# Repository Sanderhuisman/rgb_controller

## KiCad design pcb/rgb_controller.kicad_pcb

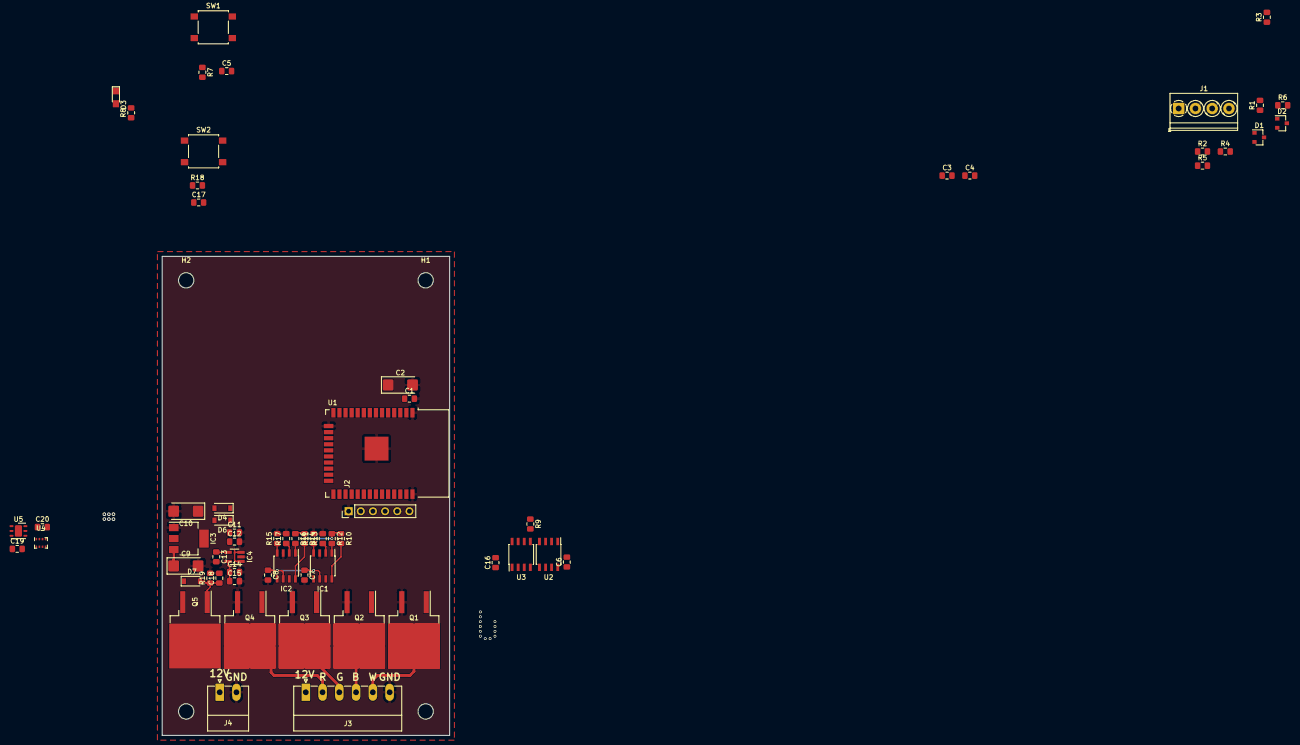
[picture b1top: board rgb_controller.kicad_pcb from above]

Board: 2 copper layers, 60.0 x 100.0 mm, 69 parts (0 on the bottom side), 40 nets.

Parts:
C1, C3, C4, C5, C6, C12, C15, C16, C17, C19, C20: 100nF; C_0805_2012Metric_Pad1.15x1.40mm_HandSolder
C2, C9, C10: 10uF; CP_EIA-6032-28_Kemet-C_Pad2.25x2.35mm_HandSolder
C7, C8: 1uF X7R; C_0805_2012Metric_Pad1.15x1.40mm_HandSolder
C11, C14: 1uF X5R; C_0805_2012Metric_Pad1.15x1.40mm_HandSolder
C13: 10nF X7R; C_0805_2012Metric_Pad1.15x1.40mm_HandSolder
C18: 15nF; C_0805_2012Metric_Pad1.15x1.40mm_HandSolder
D1, D2: BAT54S; SOT-23
D3: RED; LED_0805_HandSoldering
D4, D6: MBR0520; D_SOD-123
D7: MMSZ5240BT1G; D_SOD-123
H1, H2, H3, H4: MountingHole; MountingHole_3.2mm_M3
IC1, IC2: PM8834; SOIC-8_3.9x4.9mm_Pitch1.27mm
IC3: LD1117S50TR_SOT223; SOT-223-3_TabPin2
IC4: LD3985M33R_SOT23; SOT-23-5_HandSoldering
J1: Screw_Terminal_01x04; TerminalBlock_Phoenix_PT-1,5-4-3.5-H_1x04_P3.50mm_Horizontal
J2: COM; Pin_Header_Straight_1x06_Pitch2.54mm
J3: Screw_Terminal_01x06; PhoenixContact_MC-G_06x3.50mm_Angled
J4: Screw_Terminal_01x02; PhoenixContact_MC-G_02x3.50mm_Angled
Q1, Q2, Q3, Q4: IRF3205SPBF; TO-263-2
Q5: IRF9540N; TO-263-2
R1, R4: 10R; R_0805_2012Metric_Pad1.15x1.40mm_HandSolder
R2, R5, R8: 1K; R_0805_2012Metric_Pad1.15x1.40mm_HandSolder
R3, R6, R7, R9, R10, R11, R12, R13, R14, R15, R16, R17, R18, R19: 10K; R_0805_2012Metric_Pad1.15x1.40mm_HandSolder
SW1, SW2: SW_Push; SW_SPST_B3S-1000
U1: ESP32-WROOM-32D; ESP32-WROOM-32
U2: LM75B; SOIC-8_3.9x4.9mm_P1.27mm
U3: TSL2550D; SOIC-8_3.9x4.9mm_Pitch1.27mm
U4: BMP280; Bosch_LGA-8_2x2.5mm_P0.65mm_ClockwisePinNumbering
U5: Si7021-A20; DFN-6-1EP_3x3mm_P1mm_EP1.5x2.4mm

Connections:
+3V3: C1.1, C2.1, C6.1, C14.1, C15.1, C16.1, C19.1, C20.1, D1.1, D2.1, IC4.5, J1.1, R3.2, R6.2, R7.1, R9.1, R18.1, U1.2, U2.8, U3.1, U4.2, U4.6, U4.8
+12V: C7.1, C8.1, C9.1, D7.1, IC1.6, IC2.6, IC3.3, J3.1, Q5.3, R10.1, R12.1, R14.1, R16.1
/LED driver/DRIVER_B: J3.3, Q3.2
/LED driver/DRIVER_G: J3.4, Q2.2
/LED driver/DRIVER_R: J3.5, Q1.2
/LED driver/DRIVER_W: J3.2, Q4.2
/LED driver/LED_B: IC2.2, R17.1
/LED driver/LED_G: IC1.4, R11.1
/LED driver/LED_R: IC1.2, R13.1
/LED driver/LED_W: IC2.4, R15.1
/MCU/EN: C5.1, R7.2, SW1.1, U1.3
/MCU/I2C1_SCL: U2.2, U3.8, U4.4
/MCU/I2C1_SDA: U2.1, U3.5, U4.3
/MCU/IN1: C3.1, R2.1, R3.1
/MCU/IN2: C4.1, R5.1, R6.1
/MCU/IO0: C17.1, R18.2, SW2.1, U1.25
/MCU/IO13: R8.1, U1.16
/MCU/RXD: J2.5, U1.35
/MCU/RXD0: J2.4, U1.34
GND: C1.2, C2.2, C3.2, C4.2, C5.2, C6.2, C7.2, C8.2, C9.2, C10.2, C11.2, C12.2, C13.2, C14.2, C15.2, C16.2, C17.2, C18.2, C19.2, C20.2, D1.2, D2.2, D3.1, IC1.3, IC2.3, IC3.1, IC4.2, J1.4, J2.1, J3.6, J4.2, Q1.3, Q2.3, Q3.3, Q4.3, R11.2, R13.2, R15.2, R17.2, R19.2, SW1.2, SW2.2, U1.1, U1.15, U1.38, U1.39, U2.4, U2.5, U2.6, U2.7, U3.4, U4.1, U4.5, U4.7
unnamed: C10.1, D6.2, IC3.2
unnamed: C11.1, C12.1, D4.1, D6.1, IC4.1, IC4.3
unnamed: C13.1, IC4.4
unnamed: C18.1, D7.2, Q5.1, R19.1
unnamed: D1.3, R1.1, R2.2
unnamed: D2.3, R4.1, R5.2
unnamed: D3.2, R8.2
unnamed: IC1.1, R12.2
unnamed: IC1.5, Q2.1
unnamed: IC1.7, Q1.1
unnamed: IC1.8, R10.2
unnamed: IC2.1, R16.2
unnamed: IC2.5, Q4.1
unnamed: IC2.7, Q3.1
unnamed: IC2.8, R14.2
unnamed: J1.2, R1.2
unnamed: J1.3, R4.2
unnamed: J4.1, Q5.2
unnamed: R9.2, U2.3
VCOM: D4.2, J2.3

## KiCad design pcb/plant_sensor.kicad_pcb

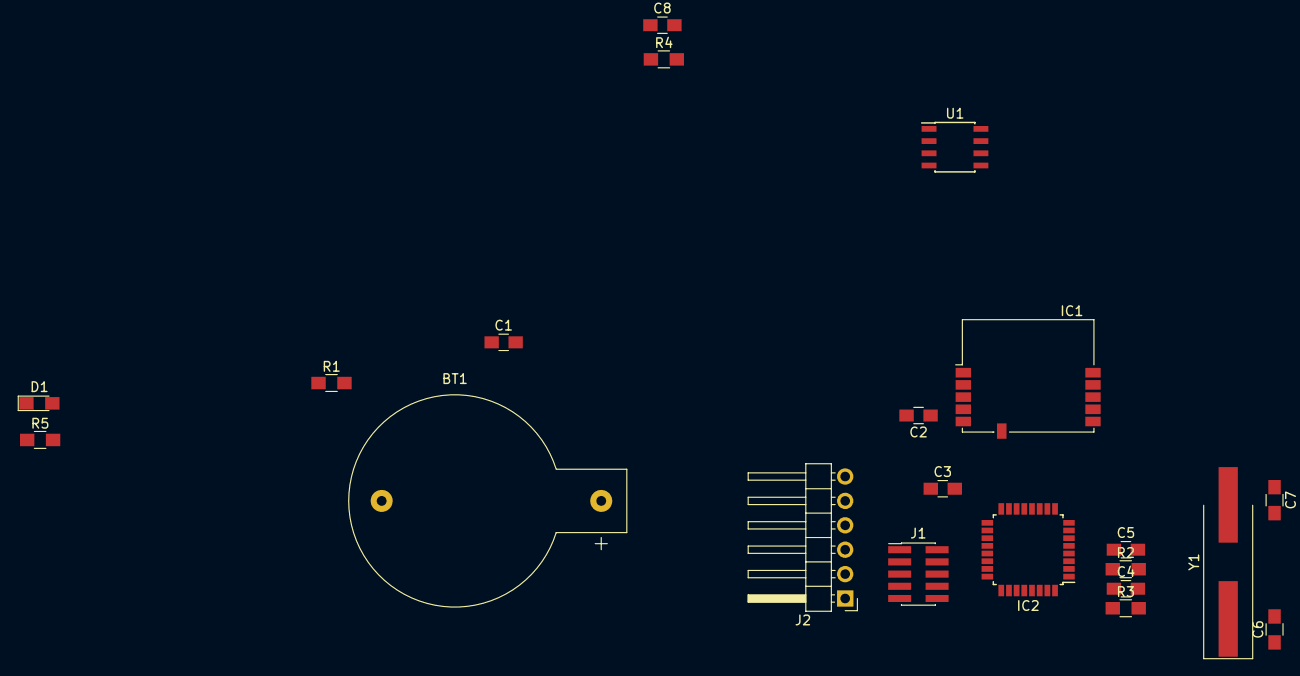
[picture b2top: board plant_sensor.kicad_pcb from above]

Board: 2 copper layers, 21 parts (0 on the bottom side), 17 nets, no tracks yet.

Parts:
BT1: CR2032; CR2032H
C1: 1uF X5R; C_0805_HandSoldering
C2: 1uF; C_0805_HandSoldering
C3, C4, C5, C8: 100nF; C_0805_HandSoldering
C6, C7: 4.3pF; R_0805_HandSoldering
D1: RED; LED_0805_HandSoldering
IC1: SPBTLE-RF0; ST_SPBTLE
IC2: STM32L052K8Tx; LQFP-32_7x7mm_Pitch0.8mm
J1: Conn_ARM_JTAG_SWD_10; Pin_Header_Straight_2x05_Pitch1.27mm_SMD
J2: COM; Pin_Header_Angled_1x06_Pitch2.54mm
R1: 47K; R_0805_HandSoldering
R2: FBead; R_0805_HandSoldering
R3, R4: 10K; R_0805_HandSoldering
R5: 1K; R_0805_HandSoldering
U1: M95256-WMN6P; SOIC-8_3.9x4.9mm_Pitch1.27mm
Y1: 32.768kHz; Crystal_SMD_HC49-SD_HandSoldering

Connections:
+3V3: C2.1, C3.1, C4.1, IC1.5, IC2.1, IC2.17, J1.1, R2.1, R4.1
+BATT: BT1.1, C1.1
/BLE/BLE_IRQ: IC1.4, R1.1
/MCU/RCC_OSC32_IN: C6.1, IC2.2, Y1.1
/MCU/RCC_OSC32_OUT: C7.1, IC2.3, Y1.2
/MCU/RXD: IC2.19, J2.5
/MCU/SPI1_CLK: IC1.7, IC2.11
/MCU/SPI1_MISO: IC1.8, IC2.12
/MCU/SPI1_MOSI: IC1.9, IC2.13
/MCU/SYS_SWCLK: IC2.24, J1.4
/MCU/SYS_SWDIO: IC2.23, J1.2
/MCU/TXD: IC2.20, J2.4
/MCU/nRESET: C8.1, IC2.4, J1.10, R4.2
GND: BT1.2, C1.2, C2.2, C3.2, C4.2, C5.2, C6.2, C7.2, C8.2, D1.1, IC1.6, IC2.16, IC2.32, J1.3, J1.5, J1.9, J2.1, R1.2, R3.2
unnamed: D1.2, R5.2
unnamed: IC2.31, R3.1
VDDA: C5.1, IC2.5, R2.2

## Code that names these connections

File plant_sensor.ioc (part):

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Mcu.Name=STM32L052K(6-8)Tx
Mcu.Package=LQFP32
Mcu.UserName=STM32L052K8Tx
PA10.Mode=Asynchronous
PA10.Signal=USART1_RX
PA11.Mode=Device
PA11.Signal=USB_DM
PA12.Mode=Device
PA12.Signal=USB_DP
PA13.Mode=Serial_Wire
PA13.Signal=SYS_SWDIO
PA14.Mode=Serial_Wire
PA14.Signal=SYS_SWCLK
PA5.Mode=Full_Duplex_Master
PA5.Signal=SPI1_SCK
PA6.Mode=Full_Duplex_Master
PA6.Signal=SPI1_MISO
PA7.Mode=Full_Duplex_Master
PA7.Signal=SPI1_MOSI
PA9.Mode=Asynchronous
PA9.Signal=USART1_TX
PB5.Mode=SMBus-Alert-mode
PB5.Signal=I2C1_SMBA
PB6.Mode=SMBus-Alert-mode
PB6.Signal=I2C1_SCL
PB7.Mode=SMBus-Alert-mode
PB7.Signal=I2C1_SDA
PC14-OSC32_IN.Mode=LSE-External-Oscillator
PC14-OSC32_IN.Signal=RCC_OSC32_IN
PC15-OSC32_OUT.Mode=LSE-External-Oscillator
PC15-OSC32_OUT.Signal=RCC_OSC32_OUT
RCC.SYSCLKFreq_VALUE=32000000
RCC.SYSCLKSource=RCC_SYSCLKSOURCE_PLLCLK
board=custom

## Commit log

2019-02-20 Initial project
2019-02-21 Added UART and further work on schematics
2019-02-22 Smaller MCU updated schematics
2019-02-22 Added temperature sensor
2019-02-23 Renamed project
2019-03-20 Layouting and update
2019-03-24 Layouting
2019-10-12 ESP wroom module
2020-03-03 backup
